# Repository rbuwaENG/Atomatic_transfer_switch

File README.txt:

░█████╗░████████╗░██████╗
██╔══██╗╚══██╔══╝██╔════╝
███████║░░░██║░░░╚█████╗░
██╔══██║░░░██║░░░░╚═══██╗
██║░░██║░░░██║░░░██████╔╝
╚═╝░░╚═╝░░░╚═╝░░░╚═════╝░
DESIGNED BY R.I BUWANEKA 
PCB,CIRCUIT DESIGNING SOLUTION 
WHATSAPP:0782532299

STEPS:
1.ARDUINO IDE-->IN PREFERENCE TICK UPLOAD 
2.THEN GET HEX FILE
1.UPLOAD HEX FILE FROM ARDUINO CODE
2.HIT PLAY BUTTON

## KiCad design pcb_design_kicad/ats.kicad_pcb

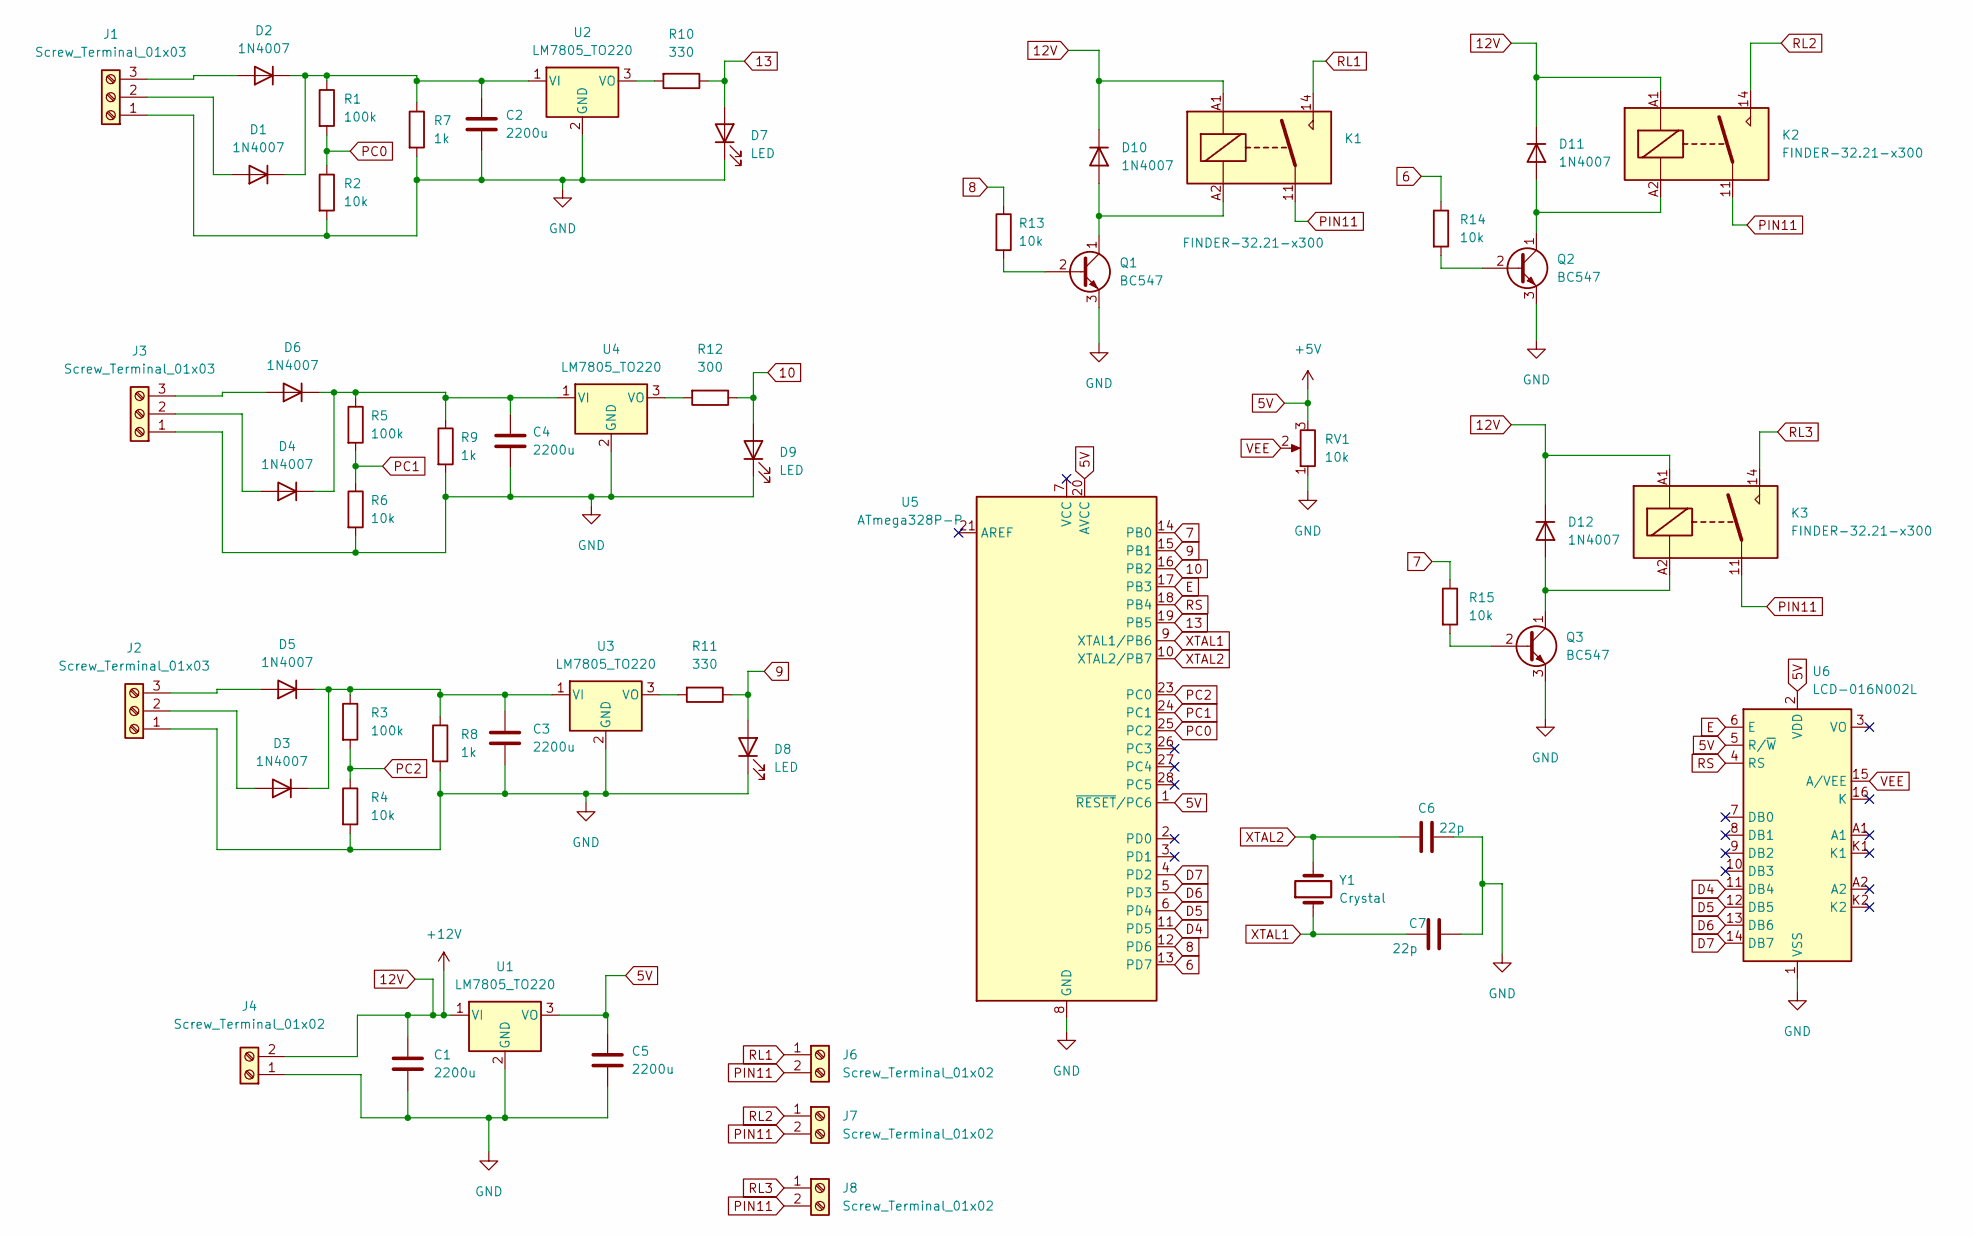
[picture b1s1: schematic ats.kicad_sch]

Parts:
C1, C2, C3, C4, C5: 2200u; C_Radial_D10.0mm_H12.5mm_P5.00mm
C6, C7: 22p; C_Disc_D6.0mm_W2.5mm_P5.00mm
D1, D2, D3, D4, D5, D6, D10, D11, D12: 1N4007; D_DO-41_SOD81_P10.16mm_Horizontal
D7, D8, D9: LED; LED_D3.0mm
J1, J2, J3: Screw_Terminal_01x03; TerminalBlock_Phoenix_MKDS-3-3-5.08_1x03_P5.08mm_Horizontal
J4: Screw_Terminal_01x02; TerminalBlock_Phoenix_MKDS-3-2-5.08_1x02_P5.08mm_Horizontal
J6, J7, J8: Screw_Terminal_01x02; TerminalBlock_Phoenix_MKDS-1,5-2-5.08_1x02_P5.08mm_Horizont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
K1, K2, K3: FINDER-32.21-x300; Relay_SPDT_Finder_36.11
Q1, Q2, Q3: BC547; TO-92_Inline
R1, R3, R5: 100k; R_Axial_DIN0204_L3.6mm_D1.6mm_P7.62mm_Horizontal
R2, R4, R6, R13, R14, R15: 10k; R_Axial_DIN0204_L3.6mm_D1.6mm_P7.62mm_Horizontal
R7, R8, R9: 1k; R_Axial_DIN0204_L3.6mm_D1.6mm_P7.62mm_Horizontal
R10, R11: 330; R_Axial_DIN0204_L3.6mm_D1.6mm_P7.62mm_Horizontal
R12: 300; R_Axial_DIN0204_L3.6mm_D1.6mm_P7.62mm_Horizontal
RV1: 10k; Potentiometer_Alps_RK163_Single_Horizontal
U1, U2, U3, U4: LM7805_TO220; TO-220-3_Vertical
U5: ATmega328P-P; DIP-28_W7.62mm
U6: LCD-016N002L
Y1: Crystal; Crystal_HC18-U_Vertical

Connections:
5V: C5.1, RV1.3, U1.3 (VO), U5.1 (~RESET/PC6), U5.20 (AVCC), U6.2 (VDD), U6.5 (R/~W)
6: R14.1, U5.13 (PD7)
7: R15.1, U5.14 (PB0)
8: R13.1, U5.12 (PD6)
9: D8.2 (A), R11.1, U5.15 (PB1)
10: D9.2 (A), R12.1, U5.16 (PB2)
12V: C1.1, D10.1 (K), D11.1 (K), D12.1 (K), J4.2, K1.A1, K2.A1, K3.A1, U1.1 (VI)
13: D7.2 (A), R10.1, U5.19 (PB5)
D4: U5.11 (PD5), U6.11 (DB4)
D5: U5.6 (PD4), U6.12 (DB5)
D6: U5.5 (PD3), U6.13 (DB6)
D7: U5.4 (PD2), U6.14 (DB7)
E: U5.17 (PB3), U6.6 (E)
GND: C1.2, C2.2, C3.2, C4.2, C5.2, C6.2, C7.2, D7.1 (K), D8.1 (K), D9.1 (K), J1.1, J2.1, J3.1, J4.1, Q1.3 (E), Q2.3 (E), Q3.3 (E), R2.2, R4.2, R6.2, R7.2, R8.2, R9.2, RV1.1, U1.2 (GND), U2.2 (GND), U3.2 (GND), U4.2 (GND), U5.8 (GND), U5.22 (GND), U6.1 (VSS)
unnamed: C2.1, D1.1 (K), D2.1 (K), R1.1, R7.1, U2.1 (VI)
unnamed: C3.1, D3.1 (K), D5.1 (K), R3.1, R8.1, U3.1 (VI)
unnamed: C4.1, D4.1 (K), D6.1 (K), R5.1, R9.1, U4.1 (VI)
unnamed: D1.2 (A), J1.2
unnamed: D2.2 (A), J1.3
unnamed: D3.2 (A), J2.2
unnamed: D4.2 (A), J3.2
unnamed: D5.2 (A), J2.3
unnamed: D6.2 (A), J3.3
unnamed: D10.2 (A), K1.A2, Q1.1 (C)
unnamed: D11.2 (A), K2.A2, Q2.1 (C)
unnamed: D12.2 (A), K3.A2, Q3.1 (C)
unnamed: Q1.2 (B), R13.2
unnamed: Q2.2 (B), R14.2
unnamed: Q3.2 (B), R15.2
unnamed: R10.2, U2.3 (VO)
unnamed: R11.2, U3.3 (VO)
unnamed: R12.2, U4.3 (VO)
PC0: R1.2, R2.1, U5.25 (PC2)
PC1: R5.2, R6.1, U5.24 (PC1)
PC2: R3.2, R4.1, U5.23 (PC0)
PIN11: J6.2, J7.2, J8.2, K1.11, K2.11, K3.11
RL1: J6.1, K1.14
RL2: J7.1, K2.14
RL3: J8.1, K3.14
RS: U5.18 (PB4), U6.4 (RS)
VEE: RV1.2, U6.15 (A/VEE)
XTAL1: C7.1, U5.9 (XTAL1/PB6), Y1.1
XTAL2: C6.1, U5.10 (XTAL2/PB7), Y1.2

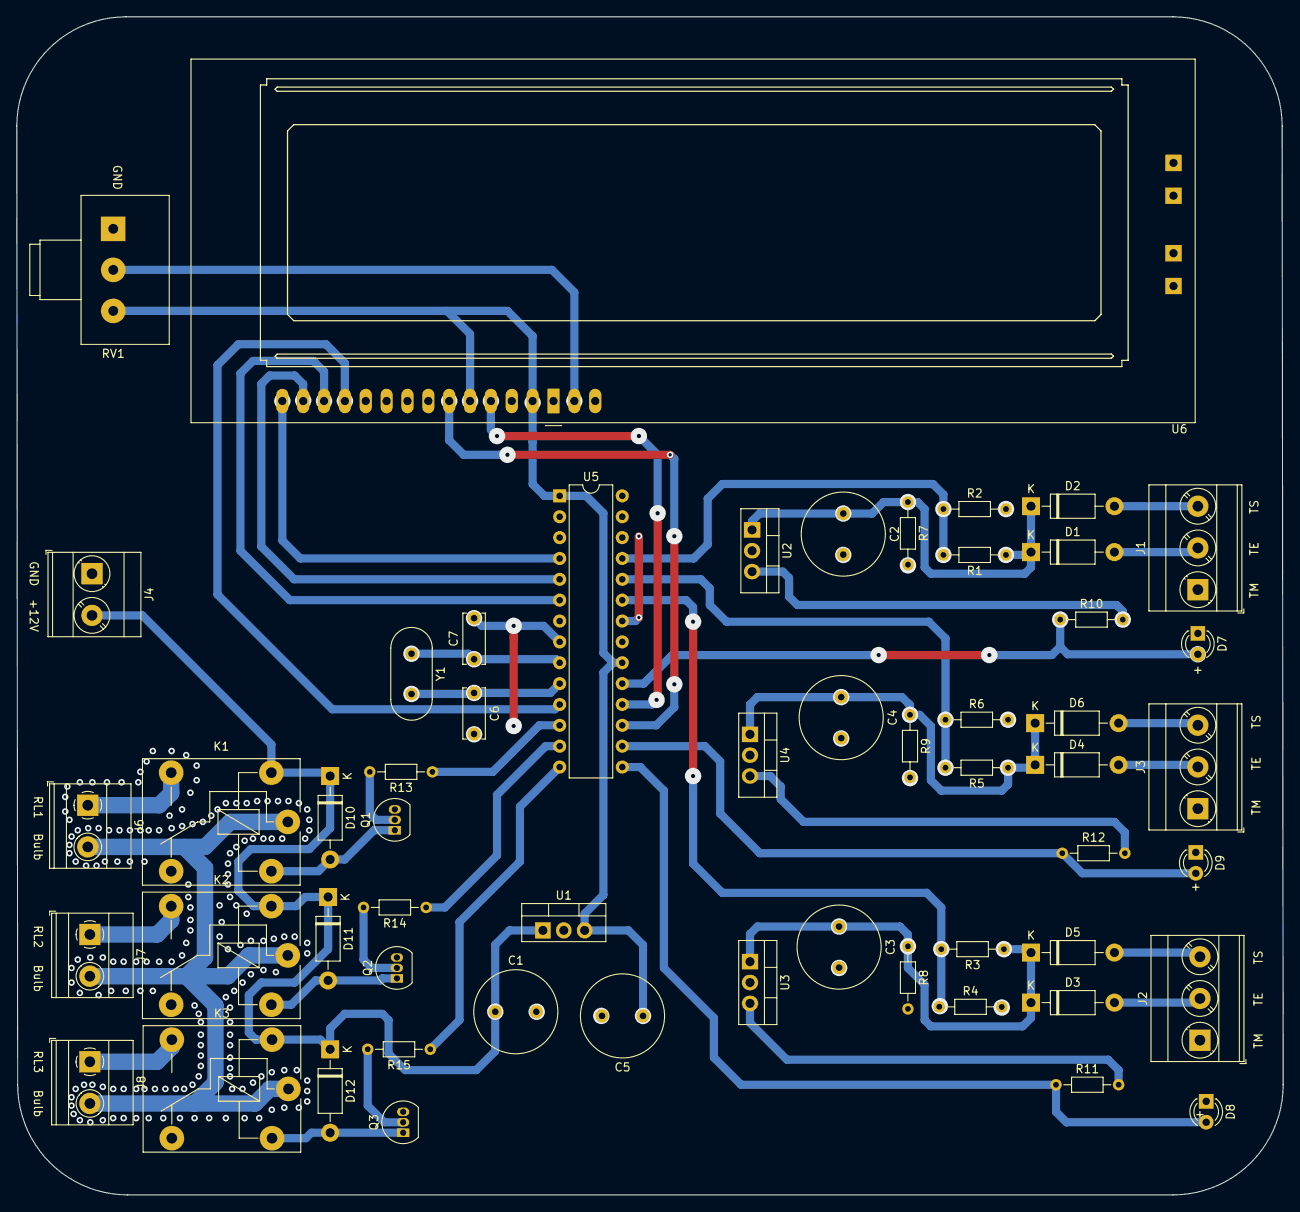
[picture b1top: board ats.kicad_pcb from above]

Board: 2 copper layers, 154.2 x 143.5 mm, 55 parts (0 on the bottom side), 43 nets.

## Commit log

2023-01-01 final project
2023-01-01 update pcb
